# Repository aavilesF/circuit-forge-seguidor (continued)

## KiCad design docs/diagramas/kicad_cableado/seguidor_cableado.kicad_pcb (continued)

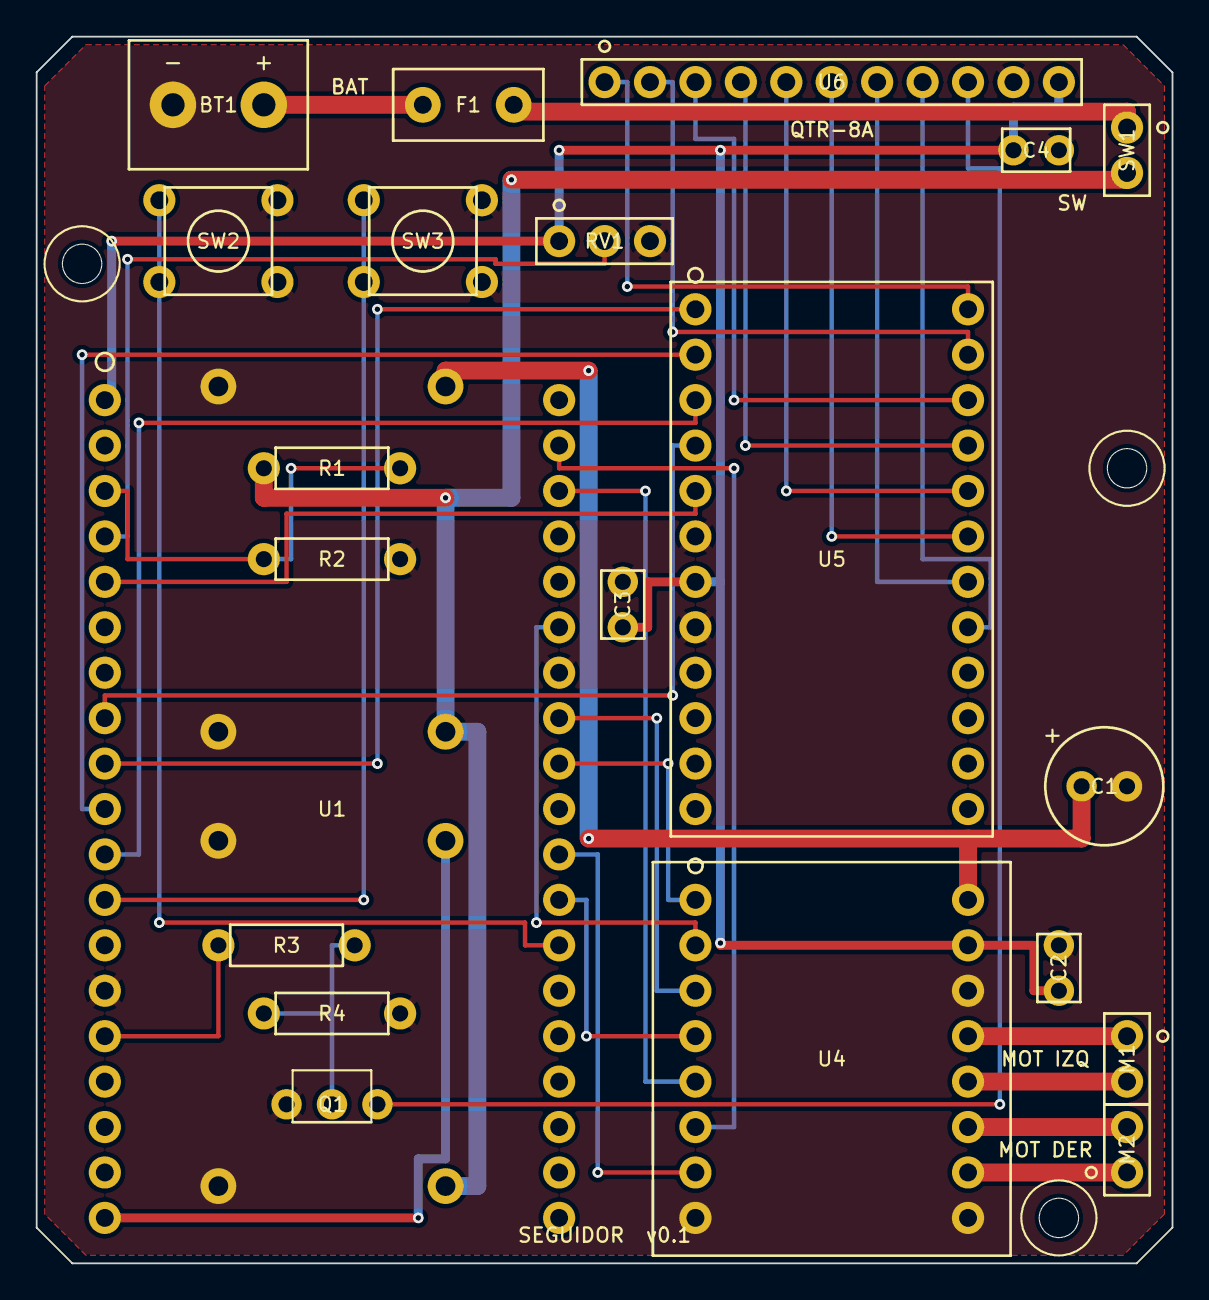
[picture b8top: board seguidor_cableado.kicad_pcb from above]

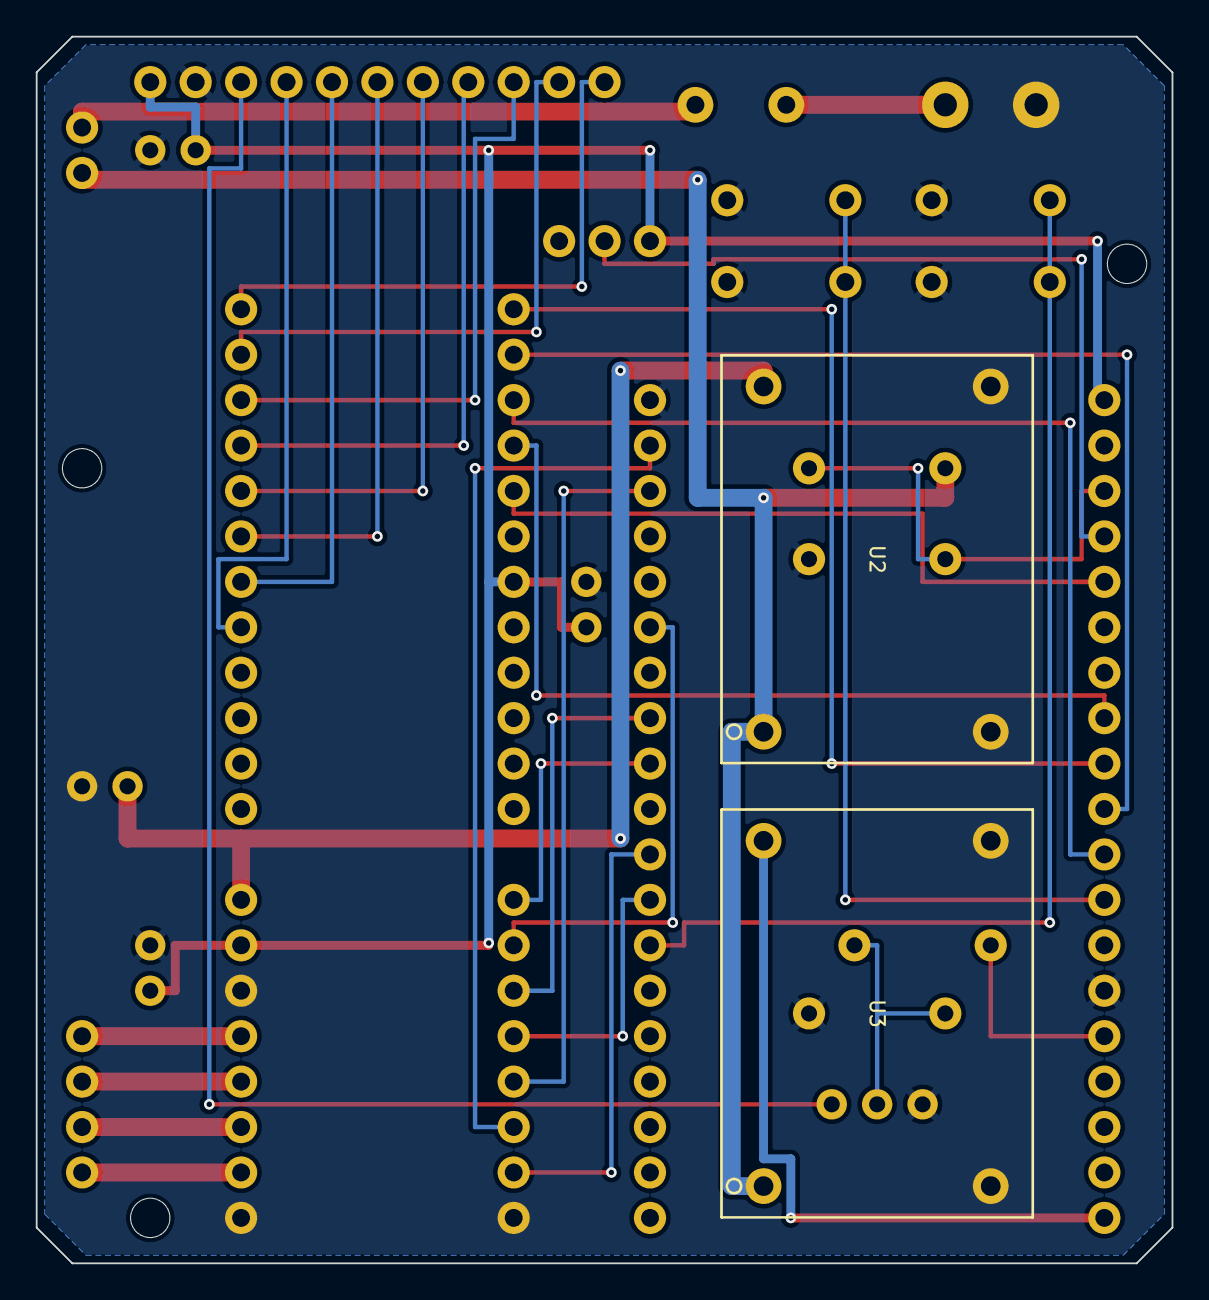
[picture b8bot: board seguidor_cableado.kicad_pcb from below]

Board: 2 copper layers, 63.5 x 68.6 mm, 26 parts (2 on the bottom side), 38 nets.

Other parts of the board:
H1, H2, H3: Agujero_M2

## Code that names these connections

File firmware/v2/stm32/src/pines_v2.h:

// GENERADO por firmware/v2/herramientas/generar_config.py desde hardware/v2/electronica/generador/principal.py.
// Funciones alternas y canales de ADC: STM32_open_pin_data (ST), STM32G474C(B-C-E)Ux [V].
#pragma once
#include <stdint.h>

namespace pin2 {

struct Gpio { char puerto; uint8_t num; uint8_t af; };
struct Analogica { char puerto; uint8_t num; uint8_t adc; uint8_t canal; };

constexpr Gpio BTN_CAL{'A', 5, 0};   // PA5
constexpr Gpio BTN_START{'C', 4, 0};   // PC4
constexpr Gpio DRV_nFAULT{'B', 12, 0};   // PB12
constexpr Gpio DRV_nSLEEP{'B', 4, 0};   // PB4
constexpr Gpio EMIT{'A', 4, 0};   // PA4
constexpr Gpio ENC_D_A{'A', 15, 1};   // PA15 AF1
constexpr Gpio ENC_D_B{'B', 3, 1};   // PB3 AF1
constexpr Gpio ENC_I_A{'B', 6, 2};   // PB6 AF2
constexpr Gpio ENC_I_B{'B', 7, 2};   // PB7 AF2
constexpr Gpio EN_D{'A', 9, 6};   // PA9 AF6
constexpr Gpio EN_I{'A', 10, 6};   // PA10 AF6
constexpr Gpio ESC_SEN{'B', 9, 1};   // PB9 AF1
constexpr Gpio I2C_SCL{'A', 8, 2};   // PA8 AF2
constexpr Gpio I2C_SDA{'C', 11, 8};   // PC11 AF8
constexpr Analogica IPROPI_D{'B', 2, 2, 12};   // PB2 ADC2_IN12
constexpr Analogica IPROPI_I{'A', 3, 1, 4};   // PA3 ADC1_IN4
constexpr Gpio LED_AMARILLO{'B', 1, 0};   // PB1
constexpr Gpio LED_ROJO{'B', 10, 0};   // PB10
constexpr Gpio LED_VERDE{'B', 0, 0};   // PB0
constexpr Gpio MUX_S0{'B', 13, 0};   // PB13
constexpr Gpio MUX_S1{'B', 14, 0};   // PB14
constexpr Gpio MUX_S2{'B', 15, 0};   // PB15
constexpr Gpio PH_D{'B', 5, 0};   // PB5
constexpr Gpio PH_I{'C', 10, 0};   // PC10
constexpr Analogica SENS_A{'A', 0, 1, 1};   // PA0 ADC1_IN1
constexpr Analogica SENS_B{'A', 1, 2, 2};   // PA1 ADC2_IN2
constexpr Analogica VBAT_MED{'A', 2, 1, 3};   // PA2 ADC1_IN3
constexpr Gpio ZUMB{'B', 8, 1};   // PB8 AF1
constexpr Gpio LED_SUCCION{'C', 6, 0};   // PC6: LED azul del módulo WeAct [V esquemático WeAct]

}  // namespace pin2

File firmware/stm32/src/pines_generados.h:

// GENERADO por herramientas/generar_config_firmware.py desde hardware/electronics/generador/diseno.py.
// NO EDITAR A MANO: los pines salen del mismo diseño que el esquemático y la PCB.
#pragma once
#include <stdint.h>

namespace pin {
struct Gpio { char puerto; uint8_t num; int8_t af; };   // af = -1: GPIO o analógico
constexpr Gpio BTN_CAL = {'C', 14, -1};   // PC14 GPIO_IN
constexpr Gpio BTN_START = {'C', 13, -1};   // PC13 GPIO_IN
constexpr Gpio DRV_FAULT = {'C', 15, -1};   // PC15 GPIO_IN
constexpr Gpio DRV_SLEEP = {'B', 10, -1};   // PB10 GPIO_OUT
constexpr Gpio EMIT_G = {'B', 9, -1};   // PB9 GPIO_OUT
constexpr Gpio ENC_L_A = {'A', 15, 1};   // PA15 TIM2_CH1
constexpr Gpio ENC_L_B = {'B', 3, 1};   // PB3 TIM2_CH2
constexpr Gpio ENC_R_A = {'B', 4, 2};   // PB4 TIM3_CH1
constexpr Gpio ENC_R_B = {'B', 5, 2};   // PB5 TIM3_CH2
constexpr Gpio LED_ERR = {'A', 12, -1};   // PA12 GPIO_OUT
constexpr Gpio LED_OK = {'B', 13, -1};   // PB13 GPIO_OUT
constexpr Gpio PWM_AIN1 = {'A', 8, 6};   // PA8 TIM1_CH1
constexpr Gpio PWM_AIN2 = {'A', 9, 6};   // PA9 TIM1_CH2
constexpr Gpio PWM_BIN1 = {'A', 11, 11};   // PA11 TIM1_CH4
constexpr Gpio PWM_BIN2 = {'A', 10, 6};   // PA10 TIM1_CH3
constexpr Gpio SWCLK = {'A', 14, 0};   // PA14 SYS_JTCK-SWCLK
constexpr Gpio SWDIO = {'A', 13, 0};   // PA13 SYS_JTMS-SWDIO
constexpr Gpio UART_RX = {'B', 7, 7};   // PB7 USART1_RX
constexpr Gpio UART_TX = {'B', 6, 7};   // PB6 USART1_TX
// Canal de TIM1 que maneja cada entrada del DRV8833
constexpr int CANAL_AIN1 = 1;
constexpr int CANAL_AIN2 = 2;
constexpr int CANAL_BIN1 = 4;
constexpr int CANAL_BIN2 = 3;
// ADC1: secuencia regular (sensor -1 = batería)
constexpr int ADC1_N = 8;
constexpr uint8_t ADC1_CANAL[ADC1_N] = {5, 11, 12, 15, 4, 3, 2, 10};
constexpr int8_t ADC1_SENSOR[ADC1_N] = {0, 1, 4, 5, 10, 11, 12, 15};
constexpr Gpio ADC1_PIN[ADC1_N] = {{'B', 14, -1}, {'B', 12, -1}, {'B', 1, -1}, {'B', 0, -1}, {'A', 3, -1}, {'A', 2, -1}, {'A', 1, -1}, {'F', 0, -1}};
// ADC2: secuencia regular (sensor -1 = batería)
constexpr int ADC2_N = 9;
constexpr uint8_t ADC2_CANAL[ADC2_N] = {14, 12, 4, 3, 13, 17, 1, 10, 15};
constexpr int8_t ADC2_SENSOR[ADC2_N] = {2, 3, 6, 7, 8, 9, 13, 14, -1};
constexpr Gpio ADC2_PIN[ADC2_N] = {{'B', 11, -1}, {'B', 2, -1}, {'A', 7, -1}, {'A', 6, -1}, {'A', 5, -1}, {'A', 4, -1}, {'A', 0, -1}, {'F', 1, -1}, {'B', 15, -1}};
constexpr float DIVISOR_VBAT = 4.030303f;   // (R3 + R4) / R4
}  // namespace pin

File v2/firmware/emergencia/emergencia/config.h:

// Robot de EMERGENCIA (placa perforada) · configuración de hardware.
// Fuente de verdad: v2/electronica/prototipo-emergencia/GUIA-FIRMWARE.md (sección 2) y el esquema unificado
// robot_emergencia_unificado.kicad_sch. NO cambiar un pin aquí sin cambiar antes el esquema (GUIA, sección 8).
// La prueba pruebas/verificar_pines.py compara este archivo con el netlist esperado del esquema.
// Marcas: [V] verificado en ficha/esquema · [C] calculado · [E] estimado · [P] pendiente de medir en el robot.
#pragma once

// ============================================================ sensores: 6 TCRT5000 por el CD74HC4067
// Montaje vigente (equipo, 21 nov 2026): SEN1..SEN6 en C0..C5; C6..C15 NO se usan. El esquema unificado todavía dibuja
// SEN7/SEN8 en C6/C7 (D-V2-41, 8 sensores): pendiente de actualizar el esquema (EM-09). Mux y pines no cambian.
#define NUM_SENSORES 6          // SEN1..SEN6 en los canales C0..C5 del mux
#define MASCARA_TODOS ((1u << NUM_SENSORES) - 1u)   // 0b111111 = 63: los 6 sensores en uso
#define PIN_MUX_S0 25           // DevKit pin 8  [V esquema]
#define PIN_MUX_S1 26           // DevKit pin 9  [V esquema]
#define PIN_MUX_S2 27           // DevKit pin 10 [V esquema]
#define PIN_MUX_S3 33           // DevKit pin 7  [V esquema]
#define PIN_MUX_SIG 34          // DevKit pin 4, ADC1_CH6, solo entrada [V esquema]
#define PIN_EMISORES 13         // EMIT_EN, DevKit pin 13: alto = LED IR encendidos (2N2222 Q1) [V esquema]
// TCRT5000 con pull-up de 10 kΩ a 3V3 y emisor a GND: más reflejo = menos voltaje [V esquema].
#define LUZ_BAJA_VOLTAJE 1
#define RESTA_AMBIENTE 1        // lee con emisores encendidos y apagados y resta (luz del lugar)

// ---- Valores INICIALES de lo que depende del montaje real. Todos se cambian sin recompilar con
// `set <clave> <valor>` + `save` (la clave va entre corchetes). Cambiarlos aquí solo cambia los de fábrica.
// Orden físico [inv_sens]: SEN1 a la izquierda y SEN6 a la derecha (equipo); FALTA confirmarlo con la barra montada
// [P]. Con la línea bajo el lado DERECHO, `sens` debe dar pos > 0; si no, `set inv_sens 1`.
#define SENSORES_INVERTIDOS 0
#define PASO_SENSORES_MM 12.7f    // [paso_mm] 5 agujeros de placa perforada, como la barra de 8 [P: medir la barra de 6]
#define DIST_SENSOR_EJE_MM 100.0f // solo informativo (la posición usa x); medir en el chasis armado (EM-06) [P]
#define MUX_ASENTAMIENTO_US 5     // [t_mux_us] espera tras cambiar S0..S3 [E: el CD74HC4067 conmuta en < 1 µs]
#define MOTOR_IZQ_INVERTIDO 0     // [inv_izq] [P] verificar con `m 0.3 0` (ruedas en el aire)
#define MOTOR_DER_INVERTIDO 1     // [inv_der] [P] los N20 van espejados; verificar con `m 0 0.3`
#define MOTORES_CRUZADOS 0        // [cruzar] 1 si el motor de AIN (M1) quedó montado del lado DERECHO

// ============================================================ DRV8833 (módulo) [V TI SLVSAR1, V esquema]
#define PIN_AIN1 19   // DevKit pin 25 · IN1 → OUT1/OUT2 = motor IZQUIERDO (M1)
#define PIN_AIN2 21   // DevKit pin 26 · IN2
#define PIN_BIN1 22   // DevKit pin 29 · IN3 → OUT3/OUT4 = motor DERECHO (M2)
#define PIN_BIN2 23   // DevKit pin 30 · IN4
#define PIN_NSLEEP 16 // DevKit pin 21 · DRV_SLEEP: alto = puente activo. Pull-down interno de 500 kΩ [V]
// nFAULT (ULT) NO está conectado (P13, D-V2-05): el firmware no lo lee.
#define PWM_FREC_HZ 20000   // inaudible; el DRV8833 acepta PWM hasta 250 kHz [V]
#define PWM_BITS 10

// ============================================================ interfaz
#define PIN_START 4       // DevKit pin 20 · botón a GND, pull-up interno [V esquema]
#define PIN_CAL 14        // DevKit pin 11 · botón a GND, pull-up interno [V esquema]
#define ANTIRREBOTE_MS 25 // lectura estable este tiempo antes de aceptar el cambio
#define PIN_LED 2         // LED azul integrado del DevKit (GPIO2 no está conectado en el esquema) [V esquema]
// Sin zumbador (D-V2-05) y sin ventilador (EM-01): no hay pines para ellos. GPIO15 y GPIO17 quedan libres.

// ============================================================ batería 2S
// Batería definitiva: pack 2S de 18650 Li-ion, 7.4 V nominal, ~2500 mAh. 8.4 V cargada (4.2 V/celda).
#define PIN_BATERIA 36    // VP, DevKit pin 2 · VBAT_SENSE [V esquema]
// Divisor NOMINAL del esquema: R1 = 100 kΩ (VBAT_SW → VBAT_SENSE) / R2 = 33 kΩ (→ GND), conectado DIRECTO a VBAT_SW
// (después del KCD1, sin diodo): no se suma caída. Factor nominal 133/33 = 4.030 (8.4 V → 2.08 V en el pin).
#define DIVISOR_BATERIA ((100.0f + 33.0f) / 33.0f)   // [C] solo referencia
// Factor EMPÍRICO que usa el firmware: punto de calibración físico del 20 nov 2026, medido al mismo tiempo, con el
// mismo GND y con el KCD1 encendido: fuente de 10.0 V → 2.1 V en VP/GPIO36 → 10.0 / 2.1 = 4.7619, offset 0 V.
// Esos 10.0 V son SOLO el punto de calibración (no el voltaje de la batería definitiva). No coincide con el nominal
// (con 4.030, 2.1 V serían 8.46 V): el divisor soldado no es exactamente 100k/33k. Pendiente: comparar `bat` con el
// multímetro usando la batería definitiva. Para volver al nominal: usar DIVISOR_BATERIA aquí.
#define FACTOR_BATERIA 4.7619f                        // [M] medido, punto único
// Máximo razonable de una 2S Li-ion: 8.4 V cargada + ~0.2 V de tolerancia (ADC calibrado de fábrica ±1–2 % y
// calibración de un solo punto). Por encima, la consola avisa (otra batería, cargador mal o lectura mal calibrada).
// Solo es aviso: no bloquea ni cambia ninguna protección.
#define BAT_MAX_2S 8.6f

// ============================================================ canales LEDC (solo arduino-esp32 2.x)
#define CANAL_AIN1 0
#define CANAL_AIN2 1
#define CANAL_BIN1 2
#define CANAL_BIN2 3

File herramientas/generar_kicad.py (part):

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# ------------------------------------------------------------------ pines (desde pines.h)
txt = (RAIZ / "firmware/seguidor/pines.h").read_text(encoding="utf-8")
PIN = {m.group(1): int(m.group(2)) for m in re.finditer(r"constexpr int\s+(PIN_\w+)\s*=\s*(\d+)", txt)}
NECESARIOS = ["PIN_MUX_S0", "PIN_MUX_S1", "PIN_MUX_S2", "PIN_MUX_S3", "PIN_MUX_SIG1", "PIN_MUX_SIG2",
              "PIN_EMISORES", "PIN_PWMA", "PIN_AIN1", "PIN_AIN2", "PIN_PWMB", "PIN_BIN1", "PIN_BIN2",
              "PIN_STBY", "PIN_START", "PIN_CAL", "PIN_LED", "PIN_PERFIL", "PIN_BATERIA"]
faltan = [k for k in NECESARIOS if k not in PIN]
if faltan:
    sys.exit(f"pines.h no define: {faltan}")
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if dup:
    sys.exit(f"GPIO repetidos en pines.h: {dup}")
SOLO_ENTRADA = {34, 35, 36, 39}
ENTRADAS = {"PIN_MUX_SIG1", "PIN_MUX_SIG2", "PIN_BATERIA", "PIN_PERFIL"}
for k in NECESARIOS:
    p = PIN[k]
    if p in {6, 7, 8, 9, 10, 11}:
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
def simbolo_esp32():
    izq = [("VIN", "VIN", "+5V"), ("3V3", "3V3", "+3V3"), ("GND", "GND", "GND")]
    for clave in ["PIN_BATERIA", "PIN_PERFIL", "PIN_MUX_SIG1", "PIN_MUX_SIG2", "PIN_START", "PIN_CAL", "PIN_LED"]:
        izq.append((str(PIN[clave]), f"GPIO{PIN[clave]}", clave[4:]))
    der = []
    for clave in ["PIN_MUX_S0", "PIN_MUX_S1", "PIN_MUX_S2", "PIN_MUX_S3", "PIN_EMISORES", "PIN_PWMA", "PIN_AIN1",
                  "PIN_AIN2", "PIN_PWMB", "PIN_BIN1", "PIN_BIN2", "PIN_STBY"]:
        der.append((str(PIN[clave]), f"GPIO{PIN[clave]}", clave[4:]))
    sym = caja("ESP32_DEVKIT_38", "U", "ESP32 DevKit (WROOM-32)", [(a, b) for a, b, _ in izq], [(a, b) for a, b, _ in der])
    return sym, izq, der
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    d.colocar(S_BUCK, "U3", "Buck 5 V (>= 1 A): ESP32", *p(62, 118))
    d.conectar("U3", "IN+", "VBAT"); d.conectar("U3", "IN-", "GND")
    d.conectar("U3", "OUT+", "+5V"); d.conectar("U3", "OUT-", "GND")
    d.texto(18, 138, "Divisor de bateria: 8.4 V -> 2.7 V en GPIO36")
    d.colocar(S_R, "R1", "100k", *p(30, 152))
    d.conectar("R1", "1", "VBAT"); d.conectar("R1", "2", "BATERIA")
    d.colocar(S_R, "R2", "47k", *p(78, 152))
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    for nombre_pin, _, red in esp_der:
        pin = [x for x in esp.pines if x["num"] == nombre_pin][0]["name"]
        d.conectar("U1", pin, red)
    d.texto(164, 116, "GPIO35 reservado: perfil de 24 canales (2.o mux).\nGPIO2: LED azul de la placa, sin componente externo.", 1.0)

    # ---------------- Motores
    d.marco(256, 20, 408, 108, "DRIVER Y MOTORES")
    d.colocar(S_TB, "U4", "TB6612FNG (modulo)", *p(318, 68))
    for pin, red in [("VM", "+6V"), ("VCC", "+3V3"), ("GND", "GND"), ("PWMA", "PWMA"), ("AIN1", "AIN1"), ("AIN2", "AIN2"),
                     ("STBY", "STBY"), ("PWMB", "PWMB"), ("BIN1", "BIN1"), ("BIN2", "BIN2")]:
        d.conectar("U4", pin, red)
    a = d.pos("U4", "AO1")
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    # ---------------- Sensores
    d.marco(256, 116, 408, 250, "SENSORES (perfil QTR-8A, 8 canales)")
    d.colocar(S_MUX, "U5", "CD74HC4067 (modulo)", *p(296, 170))
    for pin, red in [("S0", "MUX_S0"), ("S1", "MUX_S1"), ("S2", "MUX_S2"), ("S3", "MUX_S3"), ("E", "GND"),
                     ("SIG", "MUX_SIG1"), ("VCC", "+3V3"), ("GND", "GND")]:
        d.conectar("U5", pin, red)
    a = d.pos("U5", "I0")
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            "- Pinout real del ESP32 DevKit: aqui el numero de pin es el GPIO, no la posicion fisica.\n"
            "- QTR-8A: orden de salidas, sentido del voltaje sobre negro (ALTO_ES_NEGRO) y si trae pin LEDON.\n"
            "  Q1 conmuta el retorno de los LED IR (red EMIT_RTN). El QTR-8A no expone ese retorno:\n"
            "  si se usa su pin LEDON, GPIO13 iria directo a LEDON y se retiran Q1, R3 y R4\n"
            "  (revisar la logica en la ficha; con Q1 la logica quedaria invertida).\n"
            "- Consumo del sensor sobre el 3V3 de la placa y tiempo de lectura del mux a 3.3 V.\n"
            "- Nombres y orden de pines de los modulos reales (TB6612, CD74HC4067, bucks).\n"
            "- Perfil de 24 canales: 2.o CD74HC4067 en MUX_SIG2 (GPIO35) con S0-S3 compartidos.\n"
            "- Los simbolos son funcionales y sin huella (footprint) todavia.", 1.1)
    return d

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        for r, n in g:
            por_pin[(r, n)] = g
    esperado_h = {
        "PIN_MUX_S0": ("U5", "S0"), "PIN_MUX_S1": ("U5", "S1"), "PIN_MUX_S2": ("U5", "S2"), "PIN_MUX_S3": ("U5", "S3"),
        "PIN_MUX_SIG1": ("U5", "SIG"), "PIN_EMISORES": ("R3", "1"), "PIN_PWMA": ("U4", "PWMA"), "PIN_AIN1": ("U4", "AIN1"),
        "PIN_AIN2": ("U4", "AIN2"), "PIN_PWMB": ("U4", "PWMB"), "PIN_BIN1": ("U4", "BIN1"), "PIN_BIN2": ("U4", "BIN2"),
        "PIN_STBY": ("U4", "STBY"), "PIN_START": ("SW2", "1"), "PIN_CAL": ("SW3", "1"), "PIN_PERFIL": ("RV1", "W"),
        "PIN_BATERIA": ("R1", "2")}
    for clave_h, destino in esperado_h.items():
        g = por_pin[("U1", f"GPIO{PIN[clave_h]}")]
        assert destino in g and len(g) == 2 + (clave_h == "PIN_BATERIA"), f"{clave_h}: GPIO{PIN[clave_h]} no llega a {destino}: {sorted(g)}"
    assert ("U1", f"GPIO{PIN['PIN_LED']}") in reales_nc and ("U1", f"GPIO{PIN['PIN_MUX_SIG2']}") in reales_nc
    return len(refs), len(reales), len(reales_nc)

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
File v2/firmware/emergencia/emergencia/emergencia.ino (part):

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// CD74HC4067. Hardware: v2/electronica/prototipo-emergencia/GUIA-FIRMWARE.md y robot_emergencia_unificado.kicad_sch.
//
// Base (EM-07): lógica probada en PC (posición, PID, control, filtro, motor) del firmware histórico, adaptada al
// hardware vigente: 6 sensores por mux (C0..C5), START en GPIO4, sin zumbador, sin ventilador, sin nFAULT, batería medida
// directo (sin diodo) y motores a +6V_MOT (MP1584 U2).
//
// Ciclo de control a 400 Hz: leer los 6 sensores (luz ambiente restada, sobremuestreo, mediana + pasa-bajas) →
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
static void espejar_calibracion() {       // inv_sens cambió: el sensor lógico i pasa a ser el n−1−i
  for (int i = 0, j = cal.n - 1; i < j; ++i, --j) {
    const float a = cal.minimo[i], b = cal.maximo[i];
    cal.minimo[i] = cal.minimo[j]; cal.maximo[i] = cal.maximo[j];
    cal.minimo[j] = a; cal.maximo[j] = b;
  }
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}

static void imprimir_pines() {
  Serial.printf("mux S0=%d S1=%d S2=%d S3=%d SIG=%d · EMIT_EN=%d · START=%d CAL=%d · LED=%d · VBAT=%d\n", PIN_MUX_S0,
                PIN_MUX_S1, PIN_MUX_S2, PIN_MUX_S3, PIN_MUX_SIG, PIN_EMISORES, PIN_START, PIN_CAL, PIN_LED, PIN_BATERIA);
  Serial.printf("DRV8833 AIN1=%d AIN2=%d (M1) · BIN1=%d BIN2=%d (M2) · nSLEEP=%d · sin nFAULT, zumbador ni ventilador\n",
                PIN_AIN1, PIN_AIN2, PIN_BIN1, PIN_BIN2, PIN_NSLEEP);
  Serial.printf("%d sensores, paso %.2f mm, SEN1 a la %s, mascara %lu · motores: inv_izq=%d inv_der=%d cruzar=%d\n",
                NUM_SENSORES, aj.paso_mm, aj.inv_sens > 0.5f ? "DERECHA" : "izquierda", (unsigned long)mask,
                (int)aj.inv_izq, (int)aj.inv_der, (int)aj.cruzar);
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  Serial.printf("calibracion %s (contraste minimo %.0f cuentas)\n", cal_valida ? "valida" : "NO valida", aj.contraste);
  for (int i = 0; i < cal.n; ++i) {
    const int c = util::canal_de_sensor(i, NUM_SENSORES, aj.inv_sens > 0.5f);
    const float r = cal.maximo[i] - cal.minimo[i];
    Serial.printf("  pos %d = SEN%d (C%d): negro=%.0f blanco=%.0f contraste=%.0f %s\n", i + 1, c + 1, c,
                  cal.minimo[i], cal.maximo[i], r > 0 ? r : 0.0f,
                  !util::activo(mask, i) ? "(ignorado)" : (r >= aj.contraste ? "ok" : "<- FALTA"));
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    case Monitor::CRUDO: imprimir_crudo(); break;
    case Monitor::POS: Serial.printf("pos=%+6.1f mm visible=%d confianza=%.2f negros=%d\n", est.pos_mm, est.linea_visible,
                                     est.confianza, n_oscuros); break;
    case Monitor::BAT: Serial.printf("bateria %.2f V · VP %.0f mV · ADC %d · factor %.4f\n", vbat_f, hw::mv_pin_bateria(),
                                     hw::adc_crudo_bateria(), FACTOR_BATERIA); break;
    case Monitor::BOT: Serial.printf("START=%d CAL=%d\n", hw::boton_start(), hw::boton_cal()); break;
    case Monitor::NADA: break;
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      diag_mux = ia;
      hw::seleccionar_canal(ia, cfg_lect.t_mux_us);
      const util::BitsMux b = util::bits_mux(ia);
      Serial.printf("mux fijo en C%d (S3..S0 = %d%d%d%d). Mide SIG (GPIO34) con el multimetro. `mux off` para salir\n", ia,
                    b.s3, b.s2, b.s1, b.s0);
    } else Serial.println("uso: mux <0-15> | mux off");
  } else if (!strcmp(c, "emis")) {
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    else { Serial.println("uso: mon sens | crudo | pos | bat | bot   (cualquier tecla lo detiene)"); return; }
    Serial.println("monitor a 10 Hz: cualquier tecla lo detiene");
  } else if (!strcmp(c, "botones")) {
    Serial.printf("START=%s CAL=%s (lectura directa del pin)\n", hw::boton_start() ? "OPRIMIDO" : "suelto",
                  hw::boton_cal() ? "OPRIMIDO" : "suelto");
  } else if (!strcmp(c, "bat")) {
    const int crudo = hw::adc_crudo_bateria();
    const float mv = hw::mv_pin_bateria();
    Serial.printf("ADC crudo GPIO36 = %d / 4095 · VP = %.3f V\n", crudo, mv * 0.001f);
    Serial.printf("factor aplicado = %.4f (medido 10.0 V / 2.1 V) · nominal 100k/33k = %.3f (solo referencia)\n",
                  FACTOR_BATERIA, DIVISOR_BATERIA);
    Serial.printf("bateria = %.2f V ahora, %.2f V filtrada%s\n", util::volts_bateria(mv, FACTOR_BATERIA), vbat_f,
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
